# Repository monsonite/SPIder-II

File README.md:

# SPIder

An experimental 16-bit / 8-bit bit serial computer made mostly from 74HCxx series logic.

## Update - June 30th 2024.

As a pre-requisite for the SPIder design, a minimal implementation has been prototyped onto a small (110 x120mm) 4-layer pcb.

Here is a cut-down version of SHREK to test out the ALU and Program Counter logic 

This board is intended for a forthcoming educational workshop, and so a small board footprint and low component count has been chosen for keeping costs down.

It also partly removes the need to create a full prototype on solderless breadboards - which is not only time consuming to build, but prone to wiring mistakes and reliability issues.

The pcb is known as "SHREK"  - Shift Register Exploration Kit, and is based on through-hole components for easy home-construction.

The top half of the board is the ROM, SRAM and the principal shift registers - Accumulator, B- Register, Program Counter and Memory Address Register. 74HC165, 74HC595 and 74HC299 registers have been used.

The input and output to these shift registers has been brought to jumper headers, allowing serial data to be injected or reconfiguration of the interconnectivity between registers.

The ROM and SRAM parallel address and data buses  are also brought out to expansion connectors.

The lower half of the board is the combinational logic - the ALU, the instruction decoder, the half adder that increments the PC, the clock oscillator, clock-divider, and timing sequence generator.

Most of the principal signals are brought to breakout connectors.

One of my main problems was finding an efficient way of connecting the various serial bit streams. 

A 2:1 multiplexer is effectively 3 2-input nand gates and an inverter. This effectively uses a whole quad NAND 74HC00, just for a single mux.

A-O-I gates, like the 74xx51, would have been ideal  - sadly obsoleted. 

I have chosen a 74HC126 quad tristate buffer as an alternative.

Two buffer outputs are connected together as a pair, with their individual tristate controls being driven with complementary signals. This way, only the output from one buffer can appear on the output at a time. The 14 pin package conveniently makes two separate multiplexers, saving at leat one IC package.

Further svings in ICs have been made in the ALU and PC incrementer. The ALU requires a full adder and the PC incrementer requires a half adder. This can be achieved by suitably partitioning up a 74HC283, 4-bit binary adder into two separate halves. The half adder uses bit 0 and bit 1, and will never overflow into bit 2. The full adder uses bit 2 and 3 to produce the sum and the carry output.

The diagram below shows this arrangement.

The design includes a link selectable clock divider, allowing clocks from 4kHz to 4MHz to be selected by moving a jumper link (Uses a 4060 14 stage binary counter).

Another feature is a timing sequencer (74HC193 U/D counter) that can generate a variable number of pulses to allow left and right shifting and byte/nybble swapping.

Here is a simplified block diagram of the machine:

As shown in the block diagram, it uses ten, 8-bit  shift registers, arranged as five, 16-bit devices.

I have colour coded the serial data, the parallel data and the control signal paths.

Currently, the output of any of the shift registers can be multiplexed to the input of any other.

The I/O SPI register is not strictly necessary as the Accumulator could take on this role.

Not shown is a set of output parallel output lines from the ROM to the address inputs of the RAM. This allows 12-bits of the ROM output to be used to directly address the RAM.

The clock distribution paths, the reset signal, the shift register load and register clock signals have been omitted for clarity.

Accumulator   2 x 74HC299 universal, tristate shift register

B Register  2 x 74HC165 PISO shift register

PC   2 x 74HC595  SIPO shift register with output latch

MAR 2 x 74HC595

SPI I/O register 2 x 74HC299 (optional)

4-way register multiplexers - each are 1 half of a 74HC139

PC and ALU carry flipflops   1x 74HC74

ALU and PC half adder 1 x 74HC283 1 x 74HC00, 1 x 74HC86, 1 x 74HC74, 1 x 74HC126

Clock sequencer  74HC4060, 74HC4017 74HC00 74HC161

# SPIder

This project arose from the desire to build a simple 16-bit computer using 74HC series logic. Bit serial arithmetic was chosen as a means of keeping the chip count low, whilst learning how to use shift registers to perform parallel to serial conversion and data transfer.

One motivation was to create a computer from simple logic that could interface directly to serial SPI memory, peripherals and sensors. These devices need to have serial commands and data sent to them and then perform a bidirectional exchange of data with the SPI master device.

The first stage was to design a serial ROM sequencer. This is a 16-bit ROM U1 with a serial Program Counter, which when sent 16-clock pulses, will output the ROM data as a serial bit stream, and increment the program to the next address. Alternatively the PC can be loaded with a new address to jump to.

A pair of 74HC595 8-bit shift registers U7 and U8 are used as the 16-bit Program Counter. These were chosen because they have an octal register on the output, which can be used to hold the output count of the PC and keep it static for a complete machine cycle - thus effectively maintaining the 16-bit output from the ROM static for the complete machine cycle. Thus it indirectly serves as an Instruction and Data register, saving a further 2 devices.
 
U2 a 74HC86 quad 2-input XOR and U3 a quad 2 input NAND 74HC00, are configured as a half adder with an output multiplexer. The intermediate carry is held in one half of a 74HC74 dual D type flip flop U4.

This allows the PC count to either be incremented by 1, or loaded from a serial coded address packet, which can either come from the ROM, via the B-register U5 and U6 - a pair of 74HC165 8-bit parallel load shift registers, or from an external data source. 

The clock generator and timing sequencer generates a train of 16 gated clock pulses and a low going gating pulse. These are equivalent to an SPI clock and SPI /SS (slave select) signal. The rising edge at the end of this /gating signal is used to latch the output of the program counter into the internal resisters of U7 and U8.

This ROM sequencer performs the basic operations of serving serial stored data - similar in principle to an SPI flash memory.

The timing is as follows:

The timing sequence generator is a 4-bit counter U9 a 74HC193. Its overflow is used to set an SR latch U10 which is then reset after 16 cycles.

U9 and U10 are not specific to the ROM sequencer, and could be located on another board, provided that the generate the gated clock pulse train and the low going gate /SS signal.

This particular timing generator can be used to generate different lengths of pulse trains. If used on an accumulator, the different clock sequences can be used to manipulate the data - performing left and right shifts, and byte swaps.

S Field  	Operation

0101	  Left Shift 2

0110	  Left Shift 1	

0111	  No Shift	8-bit transfer

1000	  Right Shift 1

1001	  Right Shift 2

1010	  Right Shift 3		

1011	  Nybble Swap (bit shift)

1100

1110	  No Shift 16-bit transfer

Having created what is effectively a serial ROM circuit, the next task is to apply it to the wider application of a complete bit serial CPU.

ROM_Sequencer_1 adds a pair of 74HC299 shift registers to receive the output of the B-register 16-clock cycles later.

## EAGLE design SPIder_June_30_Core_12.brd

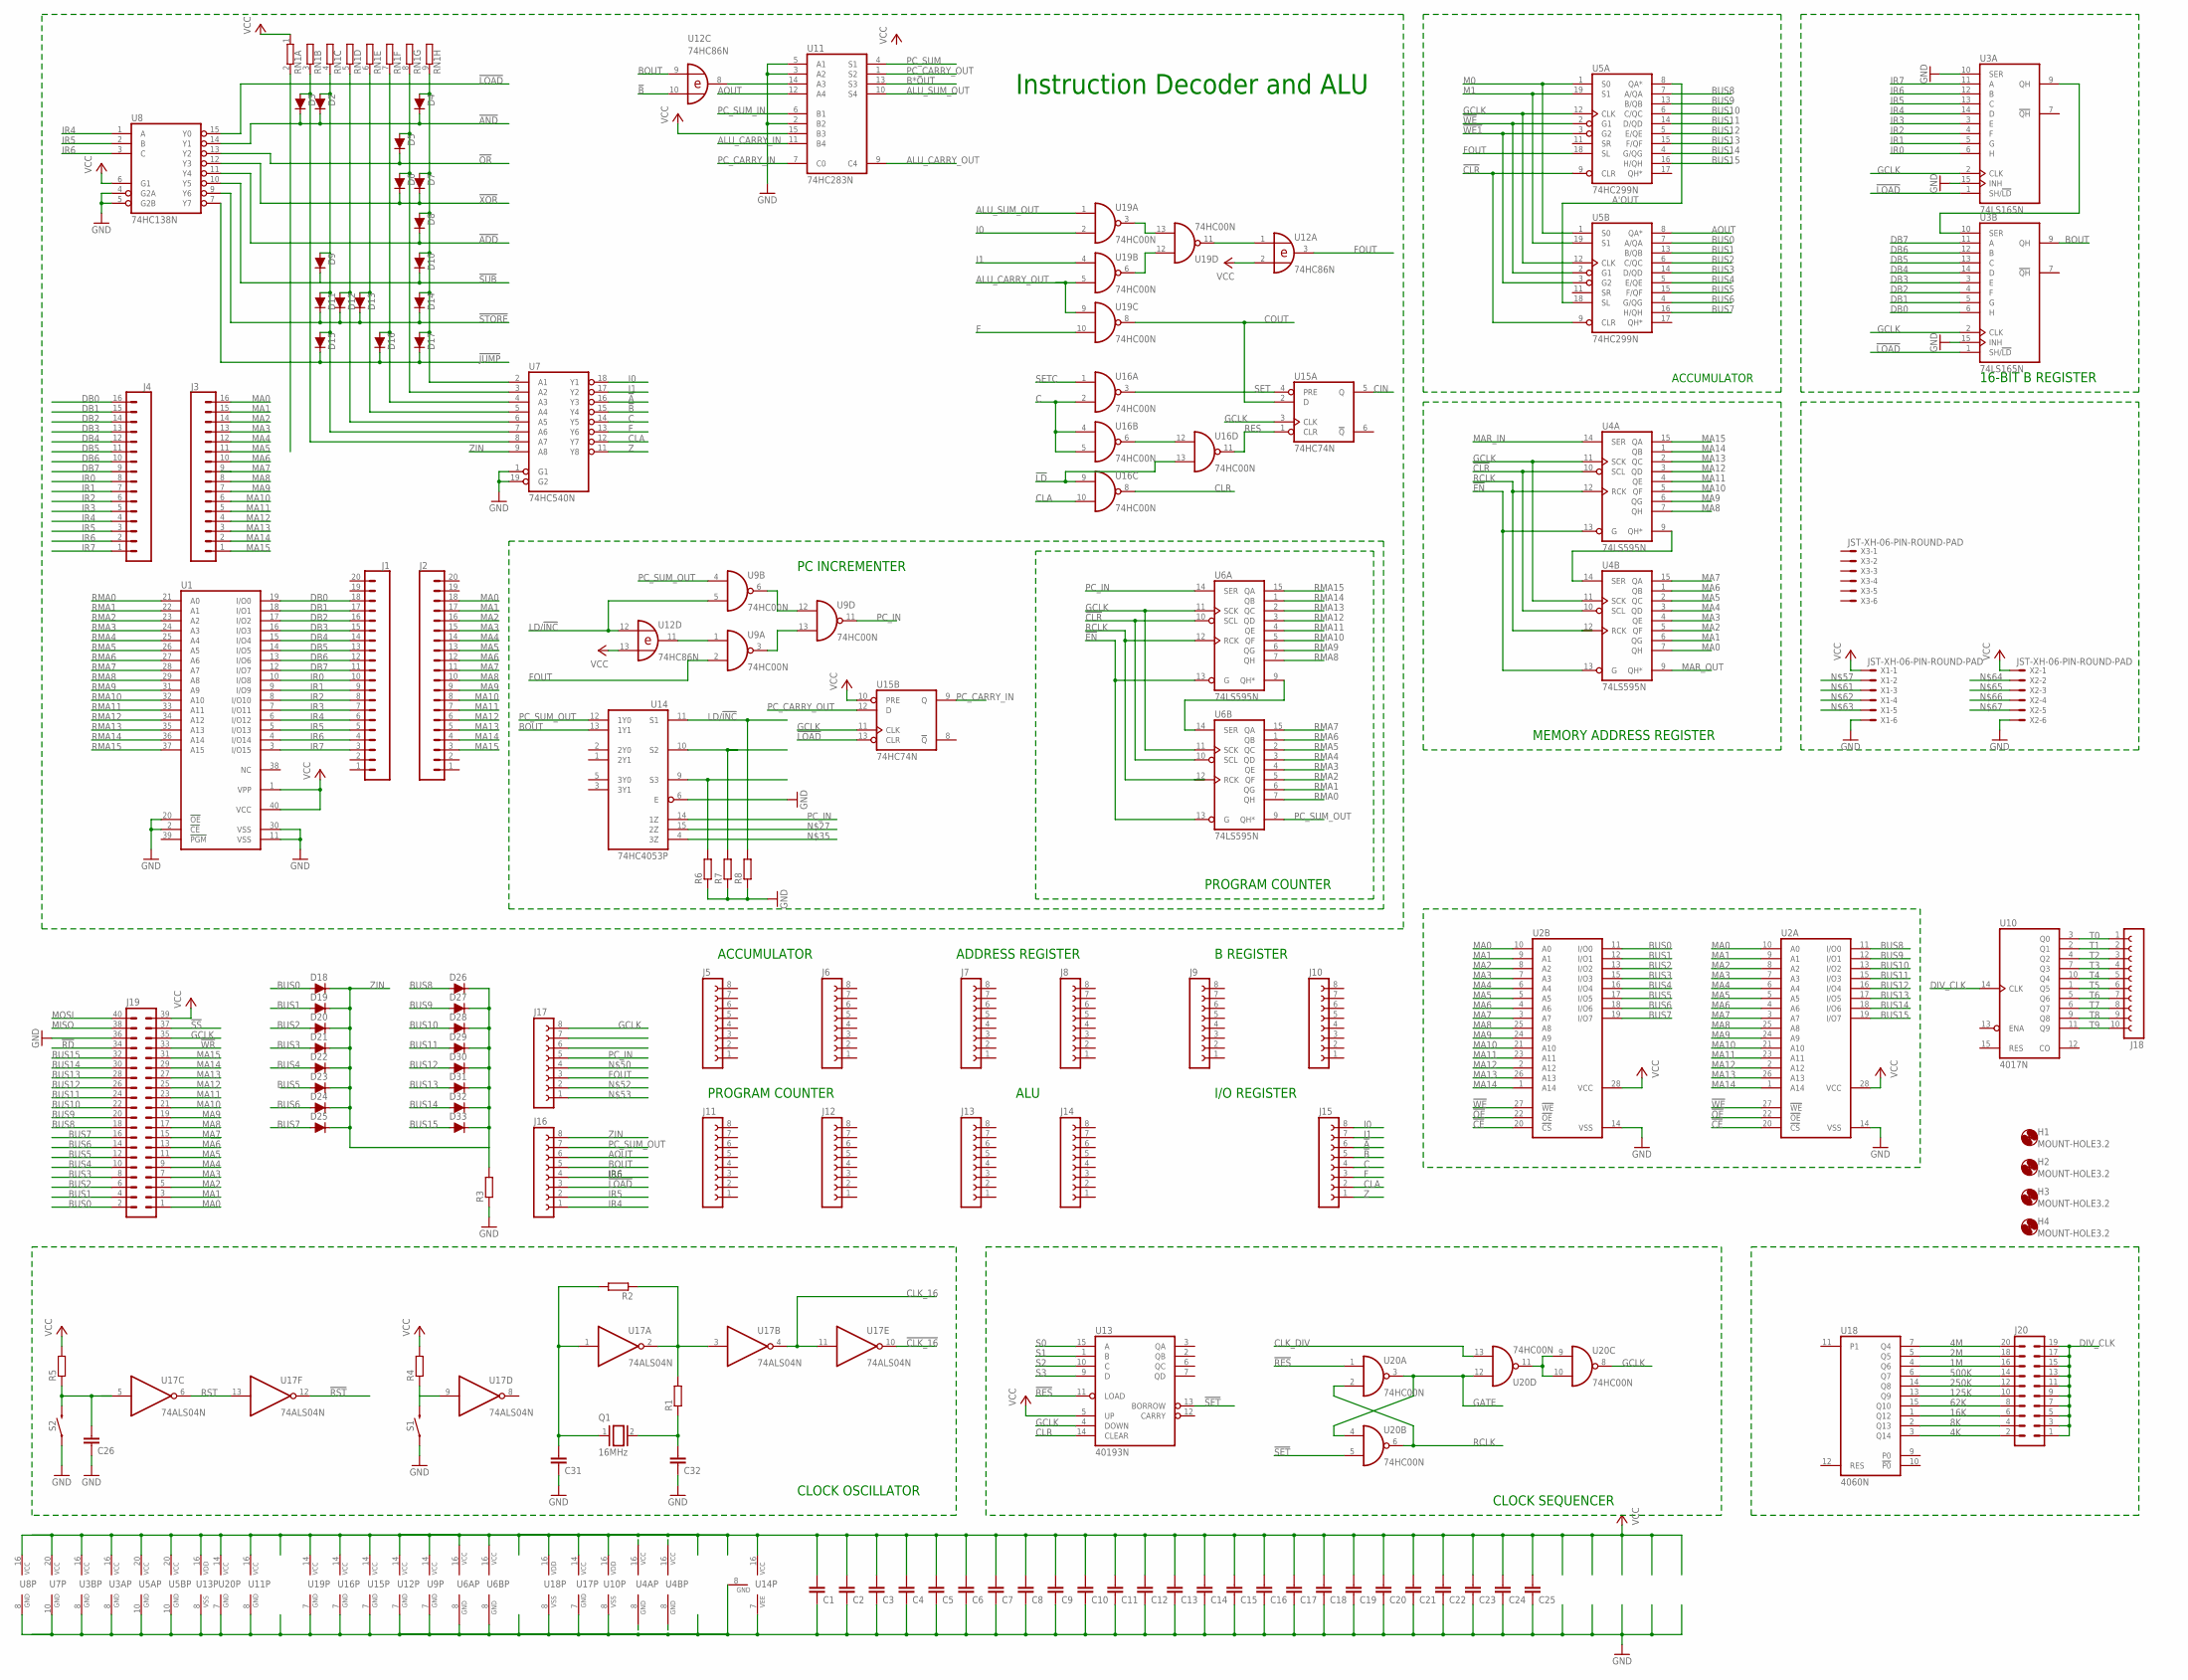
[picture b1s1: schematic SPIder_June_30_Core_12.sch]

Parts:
C1, C2, C3, C4, C5, C6, C7, C8, C9, C10, C11, C12, C13, C14, C15, C16, C17, C18, C19, C20, C21, C22, C23, C24, C25, C26, C31, C32: C-EU025-024X044; C025-024X044
D2, D3, D4, D5, D6, D7, D8, D9, D10, D11, D12, D13, D14, D15, D16, D17, D19, D20, D21, D22, D23, D24, D25, D26, D27, D28, D29, D30, D31, D32, D33: 200mA/100V/1V; DIODE-1N4148
D18: 200mA/100V/1V; DIODE-1N4148-KIT
H1, H2, H3, H4: MOUNT-HOLE3.2; 3,2
J1, J2: CONN_20NO_SILK_KIT; 1X20_NO_SILK_KIT
J3, J4: CONN_161X16_SM_SQ_NOSILK; 1X16_SM_SQ_NOSILK
J5, J6, J7, J8, J9, J10, J11, J12, J13, J14, J15, J16, J17: FE08-1; FE08
J18: FE10-1; FE10
J19: MA20-2
J20: MA10-2
Q1: 16MHz; QS
R1, R2, R3, R4, R5, R6, R7, R8: R-EU_0204/5; 0204/5
RN1: GE08R; SIL9
S1, S2: MOMENTARY-SWITCH-SPST-PTH-6.0MM; TACTILE_SWITCH_PTH_6.0MM
U1: 27C1024HG; DIL40
U2A, U2B: 62256P; DIL28-6
U3A, U3B: 74LS165N; DIL16
U4A, U4B, U6A, U6B: 74LS595N; DIL16
U5A, U5B: 74HC299N; DIL20
U7: 74HC540N; DIL20
U8: 74HC138N; DIL16
U9, U16, U19, U20: 74HC00N; DIL14
U10: 4017N; DIL16
U11: 74HC283N; DIL16
U12: 74HC86N; DIL14
U13: 40193N; DIL16
U14: 74HC4053P; DIL16
U15: 74HC74N; DIL14
U17: 74ALS04N; DIL14
U18: 4060N; DIL16
X1, X2, X3: JST-XH-06-PIN-ROUND-PAD; JST-XH-06-PACKAGE-ROUND-PAD

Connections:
1M: J20.16, U18.4 (Q6)
2M: J20.18, U18.5 (Q5)
4K: J20.2, U18.3 (Q14)
4M: J20.20, U18.7 (Q4)
8K: J20.4, U18.2 (Q13)
16K: J20.6, U18.1 (Q12)
62K: J20.8, U18.15 (Q10)
125K: J20.10, U18.13 (Q9)
250K: J20.12, U18.14 (Q8)
500K: J20.14, U18.6 (Q7)
!A: J15.6, U7.16 (Y3)
!ADD: D8.C, U8.11 (Y4)
!AND: D2.C, D3.C, D4.C, U8.14 (Y1)
!B: J15.5, U7.15 (Y4), U12.10 (I1)
!CE: U2A.20 (!CS), U2B.20 (!CS)
!CLK_16: U17.10 (O)
!CLR: U4A.10 (SCL), U4B.10 (SCL), U5A.9 (CLR), U5B.9 (CLR), U6A.10 (SCL), U6B.10 (SCL)
!EN: U4A.13 (G), U4B.13 (G), U6A.13 (G), U6B.13 (G)
!JUMP: D15.C, D16.C, D17.C, U8.7 (Y7)
!LD: U16.9 (I0), U16.13 (I1)
!LOAD: J16.3, U3A.1 (SH/!LD), U3B.1 (SH/!LD), U8.15 (Y0), U15.13 (CLR)
!OE: U2A.22 (!OE), U2B.22 (!OE)
!OR: D5.C, U8.13 (Y2)
!RD: J19.34
!RES: U13.11 (LOAD), U20.1 (I0)
!RST: U17.12 (O)
!SET: U13.13 (BORROW), U20.5 (I1)
!SS: J19.37
!STORE: D11.C, D12.C, D13.C, D14.C, U8.9 (Y6)
!SUB: D9.C, D10.C, U8.10 (Y5)
!WE: U2A.27 (!WE), U2B.27 (!WE), U5A.2 (G1), U5B.2 (G1)
!WE1: U5A.3 (G2), U5B.3 (G2)
!WR: J19.33
!XOR: D6.C, D7.C, U8.12 (Y3)
A'OUT: U5A.8 (QA*), U5B.18 (SL)
ALU_CARRY_IN: U11.11 (B4)
ALU_CARRY_OUT: U11.9 (C4), U19.5 (I1), U19.9 (I0)
ALU_SUM_OUT: U11.10 (S4), U19.1 (I0)
AOUT: J16.6, U5B.8 (QA*), U11.12 (A4)
B*OUT: U11.13 (S3)
BOUT: J16.5, U3B.9 (QH), U12.9 (I0), U14.13 (1Y1)
BUS0: D18.A, J19.2, U2B.11 (I/O0), U5B.7 (A/QA)
BUS1: D19.A, J19.4, U2B.12 (I/O1), U5B.13 (B/QB)
BUS2: D20.A, J19.6, U2B.13 (I/O2), U5B.6 (C/QC)
BUS3: D21.A, J19.8, U2B.15 (I/O3), U5B.14 (D/QD)
BUS4: D22.A, J19.10, U2B.16 (I/O4), U5B.5 (E/QE)
BUS5: D23.A, J19.12, U2B.17 (I/O5), U5B.15 (F/QF)
BUS6: D24.A, J19.14, U2B.18 (I/O6), U5B.4 (G/QG)
BUS7: D25.A, J19.16, U2B.19 (I/O7), U5B.16 (H/QH)
BUS8: D26.A, J19.18, U2A.11 (I/O0), U5A.7 (A/QA)
BUS9: D27.A, J19.20, U2A.12 (I/O1), U5A.13 (B/QB)
BUS10: D28.A, J19.22, U2A.13 (I/O2), U5A.6 (C/QC)
BUS11: D29.A, J19.24, U2A.15 (I/O3), U5A.14 (D/QD)
BUS12: D30.A, J19.26, U2A.16 (I/O4), U5A.5 (E/QE)
BUS13: D31.A, J19.28, U2A.17 (I/O5), U5A.15 (F/QF)
BUS14: D32.A, J19.30, U2A.18 (I/O6), U5A.4 (G/QG)
BUS15: D33.A, J19.32, U2A.19 (I/O7), U5A.16 (H/QH)
C: J15.4, U7.14 (Y5), U16.2 (I1), U16.4 (I0), U16.5 (I1)
CIN: U15.5 (Q)
CLA: J15.2, U7.12 (Y7), U16.10 (I1)
CLK_16: U17.4 (O), U17.11 (I)
CLK_DIV: U20.13 (I1)
CLR: U13.14 (CLEAR), U16.8 (O)
COUT: U15.2 (D), U19.8 (O)
DB0: J1.18, J4.16, U1.19 (I/O0), U3B.6 (H)
DB1: J1.17, J4.15, U1.18 (I/O1), U3B.5 (G)
DB2: J1.16, J4.14, U1.17 (I/O2), U3B.4 (F)
DB3: J1.15, J4.13, U1.16 (I/O3), U3B.3 (E)
DB4: J1.14, J4.12, U1.15 (I/O4), U3B.14 (D)
DB5: J1.13, J4.11, U1.14 (I/O5), U3B.13 (C)
DB6: J1.12, J4.10, U1.13 (I/O6), U3B.12 (B)
DB7: J1.11, J4.9, U1.12 (I/O7), U3B.11 (A)
DIV_CLK: J20.1, J20.3, J20.5, J20.7, J20.9, J20.11, J20.13, J20.15, J20.17, J20.19, U10.14 (CLK)
F: J15.3, U7.13 (Y6), U19.10 (I1)
FOUT: J17.3, U5A.18 (SL), U9.2 (I1), U12.3 (O)
GATE: U20.3 (O), U20.4 (I0), U20.12 (I0)
GCLK: J19.35, U3A.2 (CLK), U3B.2 (CLK), U4A.11 (SCK), U4B.11 (SCK), U5A.12 (CLK), U5B.12 (CLK), U6A.11 (SCK), U6B.11 (SCK), U13.4 (DOWN), U15.3 (CLK), U15.11 (CLK), U20.8 (O)
GND: C1.1, C2.1, C3.1, C4.1, C5.1, C6.1, C7.1, C8.1, C9.1, C10.1, C11.1, C12.1, C13.1, C14.1, C15.1, C16.1, C17.1, C18.1, C19.1, C20.1, C21.1, C22.1, C23.1, C24.1, C25.1, C26.1, C31.1, C32.1, J19.36, R3.1, R6.1, R7.1, R8.1, S1.1, S2.1, U1.2 (!CE), U1.11 (VSS), U1.20 (!OE), U1.30 (VSS), U2A.14 (VSS), U2B.14 (VSS), U3A.8 (GND), U3A.15 (INH), U3B.8 (GND), U3B.15 (INH), U4A.8 (GND), U4B.8 (GND), U5A.10 (GND), U5B.10 (GND), U6A.8 (GND), U6B.8 (GND), U7.1 (G1), U7.10 (GND), U7.19 (G2), U8.4 (G2A), U8.5 (G2B), U8.8 (GND), U9.7 (GND), U10.8 (VSS), U11.2 (B2), U11.3 (A2), U11.5 (A1), U11.8 (GND), U12.7 (GND), U13.8 (VSS), U14.6 (E), U14.7 (VEE), U14.8 (GND), U15.7 (GND), U16.7 (GND), U17.7 (GND), U18.8 (VSS), U19.7 (GND), U20.7 (GND), X1.6, X2.6
I0: J15.8, U7.18 (Y1), U19.2 (I1)
I1: J15.7, U7.17 (Y2), U19.4 (I0)
IR0: J1.10, J4.8, U1.10 (I/O8), U3A.6 (H)
IR1: J1.9, J4.7, U1.9 (I/O9), U3A.5 (G)
IR2: J1.8, J4.6, U1.8 (I/O10), U3A.4 (F)
IR3: J1.7, J4.5, U1.7 (I/O11), U3A.3 (E)
IR4: J1.6, J4.4, J16.1, U1.6 (I/O12), U3A.14 (D), U8.1 (A)
IR5: J1.5, J4.3, J16.2, U1.5 (I/O13), U3A.13 (C), U8.2 (B)
IR6: J1.4, J4.2, J16.4, U1.4 (I/O14), U3A.12 (B), U8.3 (C)
IR7: J1.3, J4.1, U1.3 (I/O15), U3A.11 (A)
LD/!INC: R8.2, U9.5 (I1), U12.12 (I0), U14.11 (S1)
M0: U5A.1 (S0), U5B.1 (S0)
M1: U5A.19 (S1), U5B.19 (S1)
MA0: J2.18, J3.16, J19.1, U2A.10 (A0), U2B.10 (A0), U4B.7 (QH)
MA1: J2.17, J3.15, J19.3, U2A.9 (A1), U2B.9 (A1), U4B.6 (QG)
MA2: J2.16, J3.14, J19.5, U2A.8 (A2), U2B.8 (A2), U4B.5 (QF)
MA3: J2.15, J3.13, J19.7, U2A.7 (A3), U2B.7 (A3), U4B.4 (QE)
MA4: J2.14, J3.12, J19.9, U2A.6 (A4), U2B.6 (A4), U4B.3 (QD)
MA5: J2.13, J3.11, J19.11, U2A.5 (A5), U2B.5 (A5), U4B.2 (QC)
MA6: J2.12, J3.10, J19.13, U2A.4 (A6), U2B.4 (A6), U4B.1 (QB)
MA7: J2.11, J3.9, J19.15, U2A.3 (A7), U2B.3 (A7), U4B.15 (QA)
MA8: J2.10, J3.8, J19.17, U2A.25 (A8), U2B.25 (A8), U4A.7 (QH)
MA9: J2.9, J3.7, J19.19, U2A.24 (A9), U2B.24 (A9), U4A.6 (QG)
MA10: J2.8, J3.6, J19.21, U2A.21 (A10), U2B.21 (A10), U4A.5 (QF)
MA11: J2.7, J3.5, J19.23, U2A.23 (A11), U2B.23 (A11), U4A.4 (QE)
MA12: J2.6, J3.4, J19.25, U2A.2 (A12), U2B.2 (A12), U4A.3 (QD)
MA13: J2.5, J3.3, J19.27, U2A.26 (A13), U2B.26 (A13), U4A.2 (QC)
MA14: J2.4, J3.2, J19.29, U2A.1 (A14), U2B.1 (A14), U4A.1 (QB)
MA15: J2.3, J3.1, J19.31, U4A.15 (QA)
MAR_IN: U4A.14 (SER)
MAR_OUT: U4B.9 (QH*)
MISO: J19.38
MOSI: J19.40
unnamed: U3A.9 (QH), U3B.10 (SER)
unnamed: U6A.9 (QH*), U6B.14 (SER)
unnamed: R6.2, U14.9 (S3)
unnamed: U16.6 (O), U16.12 (I0)
unnamed: U20.9 (I0), U20.10 (I1), U20.11 (O)
unnamed: R4.1, S1.3 (2), U17.9 (I)
unnamed: C26.2, R5.1, S2.3 (2), U17.5 (I)
unnamed: U12.1 (I0), U19.11 (O)
unnamed: U11.14 (A3), U12.8 (O)
unnamed: R7.2, U14.10 (S2)
unnamed: U19.3 (O), U19.13 (I1)
unnamed: U19.6 (O), U19.12 (I0)
unnamed: U9.1 (I0), U12.11 (O)
unnamed: D3.A, RN1.3 (2), U7.8 (A7)
unnamed: D2.A, D9.A, D11.A, D15.A, RN1.4 (2), U7.7 (A6)
unnamed: D12.A, RN1.5 (2), U7.6 (A5)
unnamed: U9.3 (O), U9.13 (I1)
unnamed: U9.6 (O), U9.12 (I0)
unnamed: D13.A, RN1.6 (2), U7.5 (A4)
unnamed: C31.2, Q1.1, R2.2, U17.1 (I)
unnamed: C32.2, Q1.2, R1.1
unnamed: R1.2, R2.1, U17.2 (O), U17.3 (I)
unnamed: D16.A, RN1.7 (2), U7.4 (A3)
unnamed: U4A.9 (QH*), U4B.14 (SER)
unnamed: D5.A, D6.A, RN1.8 (2), U7.3 (A2)
unnamed: D4.A, D7.A, D8.A, D10.A, D14.A, D17.A, RN1.9 (2), U7.2 (A1)
PC_CARRY_IN: U11.7 (C0), U15.9 (Q)
PC_CARRY_OUT: U11.1 (S2), U15.12 (D)
PC_IN: J17.5, U6A.14 (SER), U9.11 (O), U14.14 (1Z)
PC_SUM: U11.4 (S1)
PC_SUM_IN: U11.6 (B1)
PC_SUM_OUT: J16.7, U6B.9 (QH*), U9.4 (I0), U14.12 (1Y0)
RCLK: U4A.12 (RCK), U4B.12 (RCK), U6A.12 (RCK), U6B.12 (RCK), U20.2 (I1), U20.6 (O)
RES: U15.1 (CLR), U16.11 (O)
RMA0: U1.21 (A0), U6B.7 (QH)
RMA1: U1.22 (A1), U6B.6 (QG)
RMA2: U1.23 (A2), U6B.5 (QF)
RMA3: U1.24 (A3), U6B.4 (QE)
RMA4: U1.25 (A4), U6B.3 (QD)
RMA5: U1.26 (A5), U6B.2 (QC)
RMA6: U1.27 (A6), U6B.1 (QB)
RMA7: U1.28 (A7), U6B.15 (QA)
RMA8: U1.29 (A8), U6A.7 (QH)
RMA9: U1.31 (A9), U6A.6 (QG)
RMA10: U1.32 (A10), U6A.5 (QF)
RMA11: U1.33 (A11), U6A.4 (QE)
RMA12: U1.34 (A12), U6A.3 (QD)
RMA13: U1.35 (A13), U6A.2 (QC)
RMA14: U1.36 (A14), U6A.1 (QB)
RMA15: U1.37 (A15), U6A.15 (QA)
RST: U17.6 (O), U17.13 (I)
S0: U13.15 (A)
S1: U13.1 (B)
S2: U13.10 (C)
S3: U13.9 (D)
SET: U15.4 (PRE), U16.3 (O)
SETC: U16.1 (I0)
T0: J18.1, U10.3 (Q0)
T1: J18.2, U10.2 (Q1)
T2: J18.3, U10.4 (Q2)
T3: J18.4, U10.7 (Q3)
T4: J18.5, U10.10 (Q4)
T5: J18.6, U10.1 (Q5)
T6: J18.7, U10.5 (Q6)
T7: J18.8, U10.6 (Q7)
T8: J18.9, U10.9 (Q8)
T9: J18.10, U10.11 (Q9)
VCC: C1.2, C2.2, C3.2, C4.2, C5.2, C6.2, C7.2, C8.2, C9.2, C10.2, C11.2, C12.2, C13.2, C14.2, C15.2, C16.2, C17.2, C18.2, C19.2, C20.2, C21.2, C22.2, C23.2, C24.2, C25.2, J19.39, R4.2, R5.2, RN1.1, U1.1 (VPP), U1.40 (VCC), U2A.28 (VCC), U2B.28 (VCC), U3A.16 (VCC), U3B.16 (VCC), U4A.16 (VCC), U4B.16 (VCC), U5A.20 (VCC), U5B.20 (VCC), U6A.16 (VCC), U6B.16 (VCC), U7.20 (VCC), U8.6 (G1), U8.16 (VCC), U9.14 (VCC), U10.16 (VDD), U11.15 (B3), U11.16 (VCC), U12.2 (I1), U12.13 (I1), U12.14 (VCC), U13.5 (UP), U13.16 (VDD), U14.16 (VCC), U15.10 (PRE), U15.14 (VCC), U16.14 (VCC), U17.14 (VCC), U18.16 (VDD), U19.14 (VCC), U20.14 (VCC), X1.1, X2.1
Z: J15.1, U7.11 (Y8)
ZIN: D18.C, D19.C, D20.C, D21.C, D22.C, D23.C, D24.C, D25.C, D26.C, D27.C, D28.C, D29.C, D30.C, D31.C, D32.C, D33.C, J16.8, R3.2, U7.9 (A8)

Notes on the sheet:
Instruction Decoder and ALU
PC INCREMENTER
CLOCK SEQUENCER
ACCUMULATOR
PROGRAM COUNTER
16-BIT B REGISTER
CLOCK OSCILLATOR
B REGISTER
ALU
ADDRESS REGISTER
I/O REGISTER
MEMORY ADDRESS REGISTER

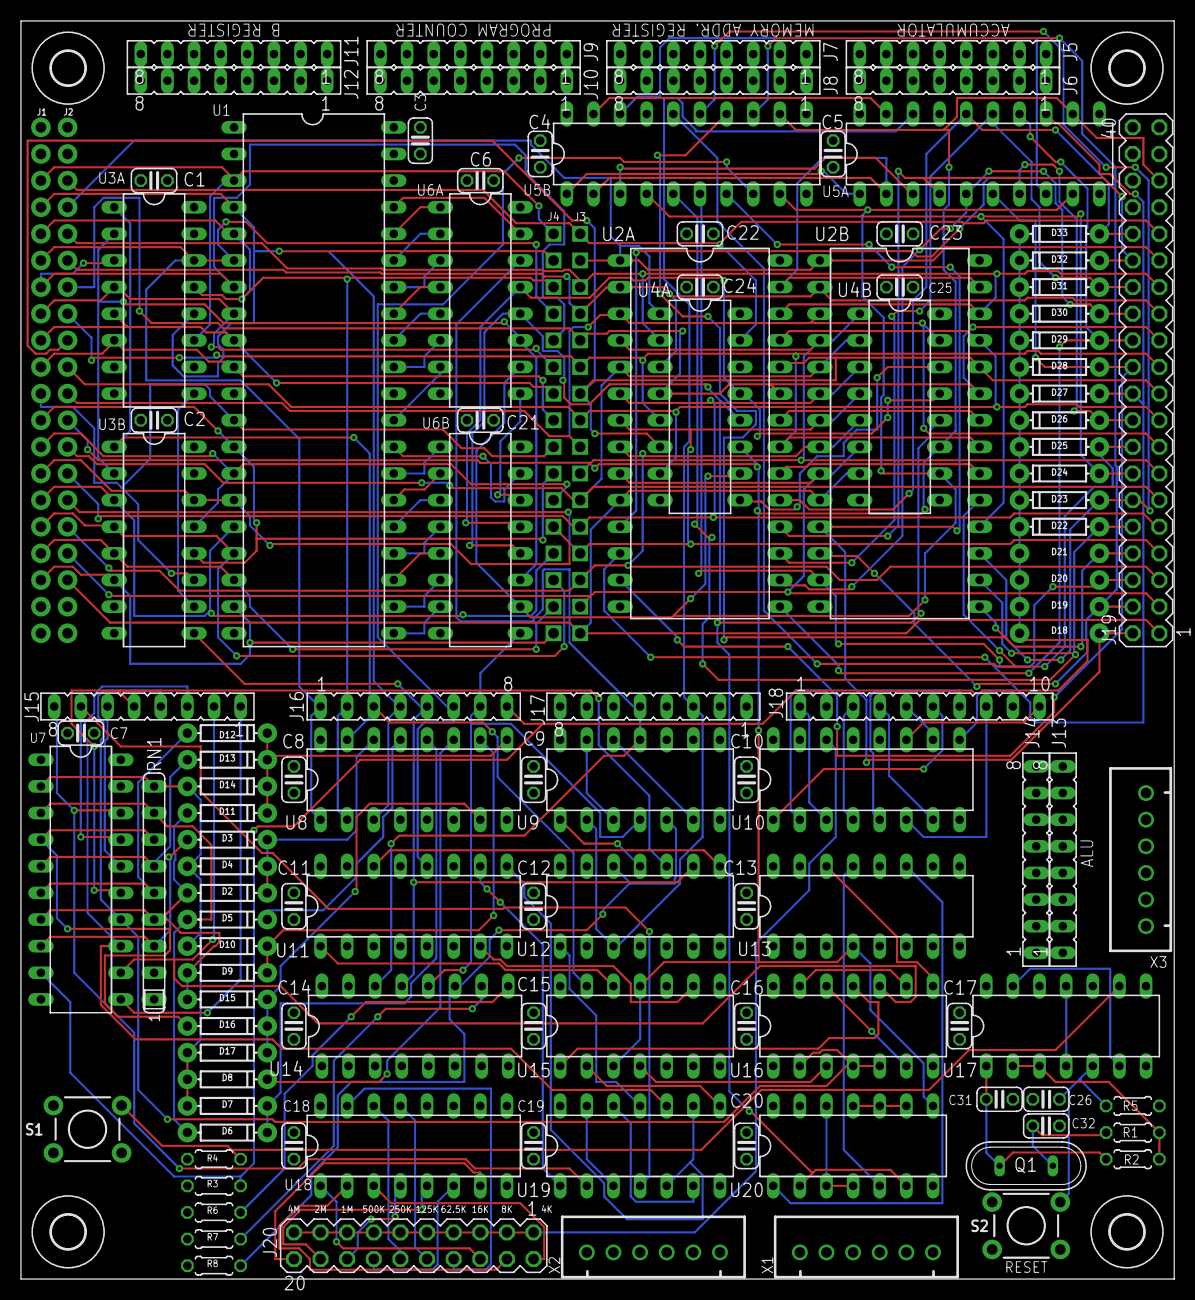
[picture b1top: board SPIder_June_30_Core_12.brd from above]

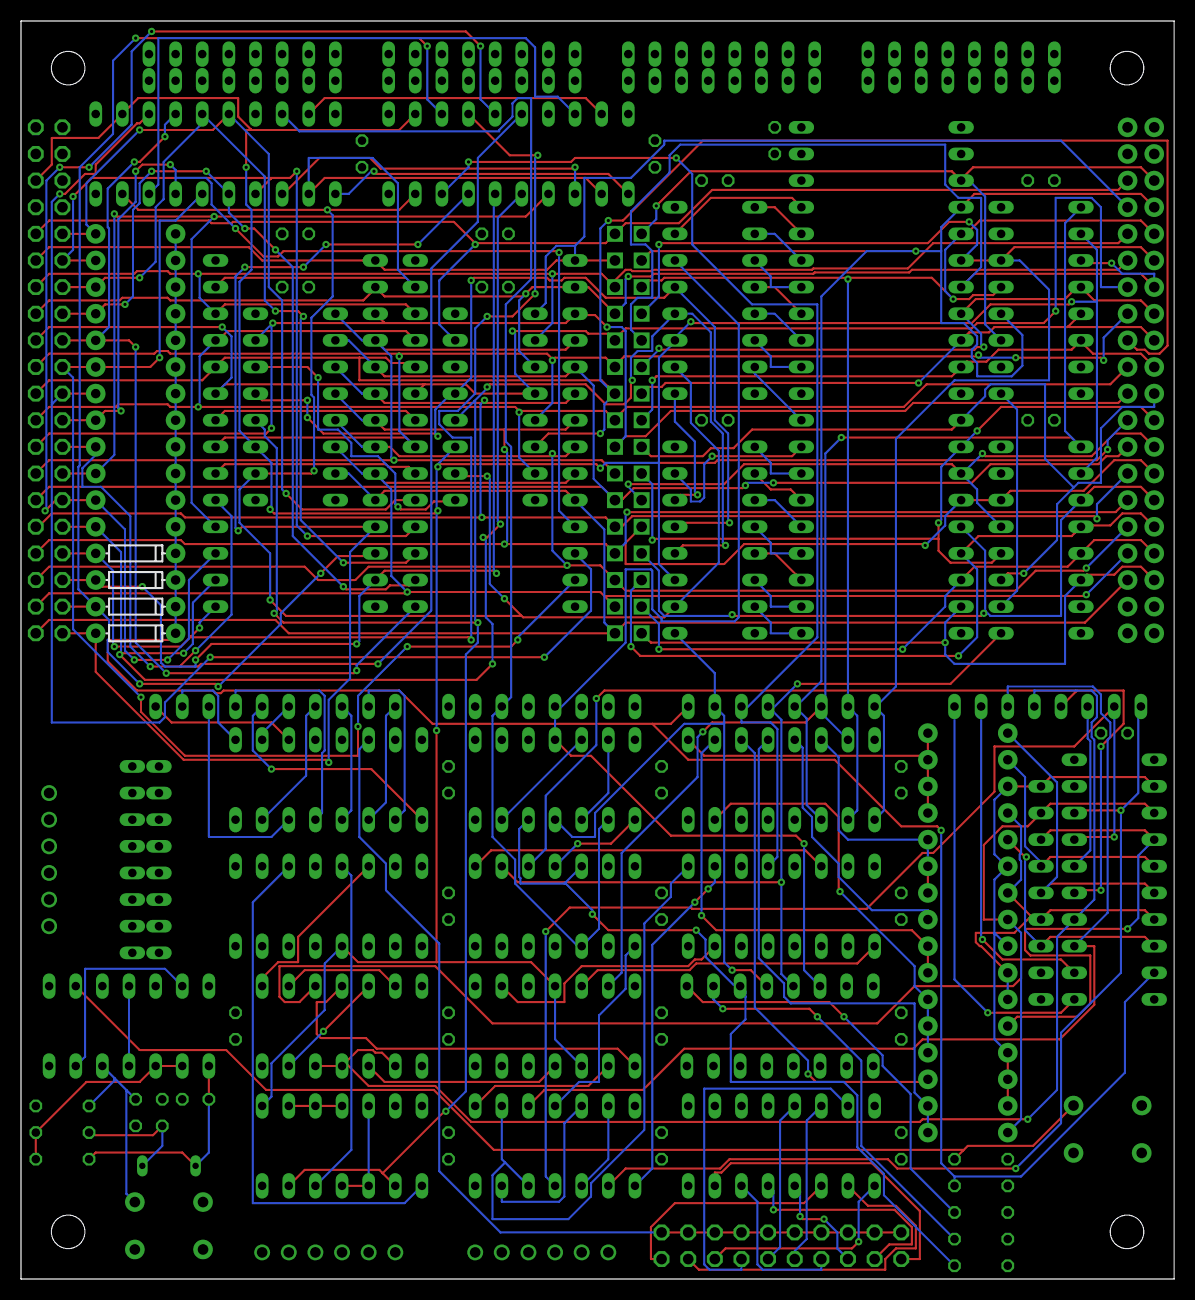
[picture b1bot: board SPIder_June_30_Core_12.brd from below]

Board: 4 copper layers, 110.0 x 120.0 mm, 124 parts (4 on the bottom side), 161 nets.

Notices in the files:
parts and their libraries:
SparkFun-LED: Licensing: Creative Commons ShareAlike 4.0 International - https://creativecommons.org/licenses/by-sa/4.0
